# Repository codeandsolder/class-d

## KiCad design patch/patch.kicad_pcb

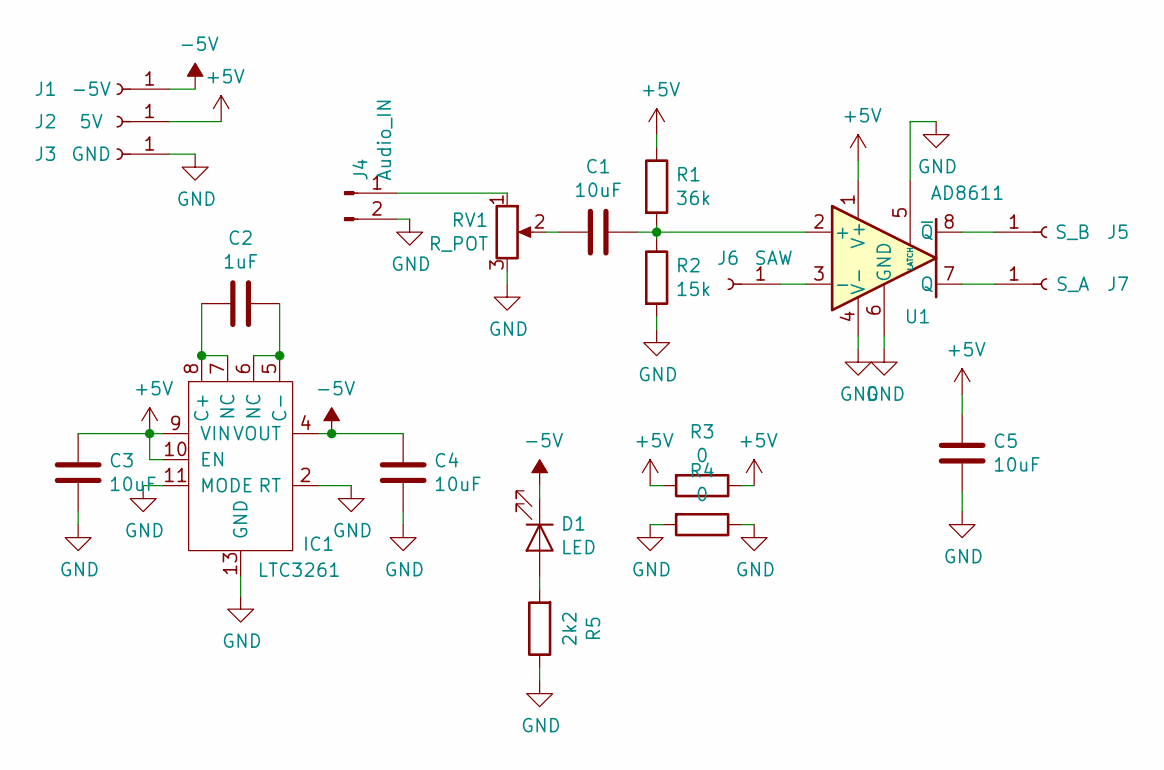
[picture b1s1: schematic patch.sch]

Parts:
C1, C3, C4, C5: 10uF; C_1206_HandSoldering
C2: 1uF; C_1206_HandSoldering
D1: LED; LED_1206_HandSoldering
IC1: LTC3261; MSOP-12-1EP_3x4mm_Pitch0.65mm
J1: -5V; SolderWirePad_single_SMD_5x10mm
J2: 5V; SolderWirePad_single_SMD_5x10mm
J3: GND; SolderWirePad_single_SMD_5x10mm
J4: Audio_IN; Pin_Header_Straight_1x02_Pitch2.54mm
J5: S_B; SolderWirePad_single_SMD_5x10mm
J6: SAW; SolderWirePad_single_SMD_5x10mm
J7: S_A; SolderWirePad_single_SMD_5x10mm
R1: 36k; R_1206_HandSoldering
R2: 15k; R_1206_HandSoldering
R3, R4: 0; R_1206_HandSoldering
R5: 2k2; R_1206_HandSoldering
RV1: R_POT; Potentiometer_Trimmer_Bourns_3266Y
U1: AD8611; SOIC-8_3.9x4.9mm_Pitch1.27mm

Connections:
+5V: C3.2, C5.2, IC1.9 (VIN), IC1.10 (EN), J2.1, R1.1, R3.1, R3.2, U1.1 (V+)
-5V: C4.2, D1.1 (K), IC1.4 (VOUT), J1.1
GND: C3.1, C4.1, C5.1, IC1.2 (RT), IC1.11 (MODE), IC1.13 (GND), J3.1, J4.2, R2.2, R4.1, R4.2, R5.1, RV1.3, U1.4 (V-), U1.5 (LATCH), U1.6 (GND)
unnamed: C1.1, RV1.2
unnamed: C1.2, R1.2, R2.1, U1.2 (+)
unnamed: C2.1, IC1.5 (C-), IC1.6 (NC)
unnamed: C2.2, IC1.7 (NC), IC1.8 (C+)
unnamed: D1.2 (A), R5.2
unnamed: J4.1, RV1.1
unnamed: J5.1, U1.8 (~Q)
unnamed: J6.1, U1.3 (-)
unnamed: J7.1, U1.7 (Q)

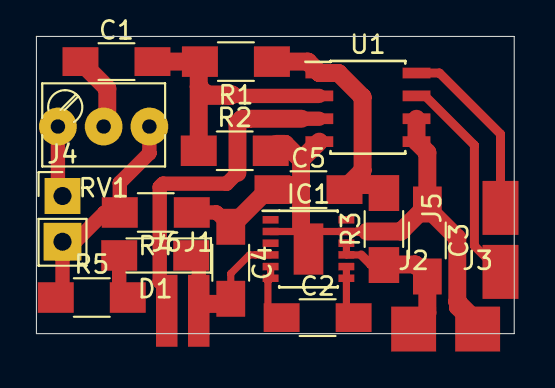
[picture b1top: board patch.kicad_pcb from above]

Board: 2 copper layers, 26.5 x 16.5 mm, 21 parts (0 on the bottom side), 12 nets.

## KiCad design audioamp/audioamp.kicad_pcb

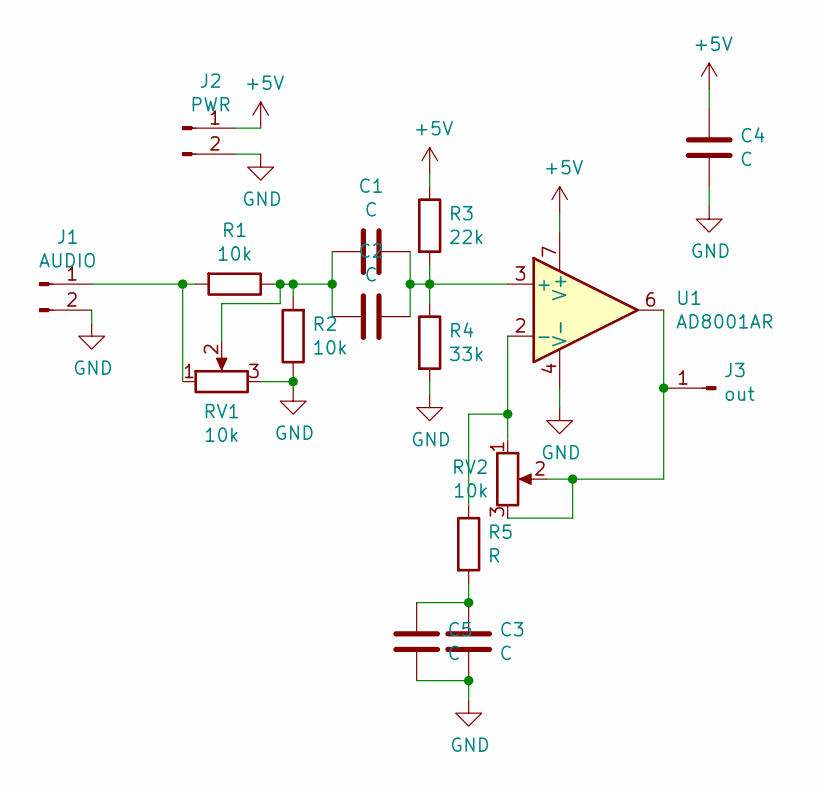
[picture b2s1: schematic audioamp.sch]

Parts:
C1, C2, C3, C4, C5: C; C_1206_3216Metric_Pad1.42x1.75mm_HandSolder
J1: AUDIO; PinHeader_1x02_P2.54mm_Vertical
J2: PWR; PinHeader_1x02_P2.54mm_Vertical
J3: out; PinHeader_1x01_P2.54mm_Vertical
R1, R2: 10k; R_1206_3216Metric_Pad1.42x1.75mm_HandSolder
R3: 22k; R_1206_3216Metric_Pad1.42x1.75mm_HandSolder
R4: 33k; R_1206_3216Metric_Pad1.42x1.75mm_HandSolder
R5: R; R_1206_3216Metric_Pad1.42x1.75mm_HandSolder
RV1: 10k; Potentiometer_Alps_RK163_Single_Horizontal
RV2: 10k; Potentiometer_Bourns_3296W_Vertical
U1: AD8001AR; SOIC-8_3.9x4.9mm_P1.27mm

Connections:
+5V: C4.1, J2.1, R3.1, U1.7 (V+)
GND: C3.2, C4.2, C5.2, J1.2, J2.2, R2.1, R4.2, RV1.3, U1.4 (V-)
unnamed: C1.1, C2.1, R1.1, R2.2, RV1.2
unnamed: C1.2, C2.2, R3.2, R4.1, U1.3 (+)
unnamed: C3.1, C5.1, R5.2
unnamed: J1.1, R1.2, RV1.1
unnamed: J3.1, RV2.2, RV2.3, U1.6
unnamed: R5.1, RV2.1, U1.2 (-)

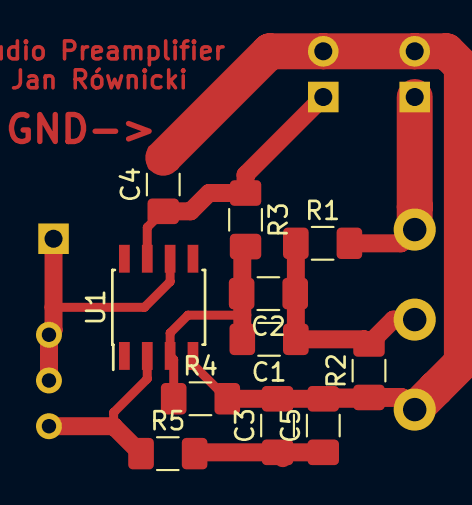
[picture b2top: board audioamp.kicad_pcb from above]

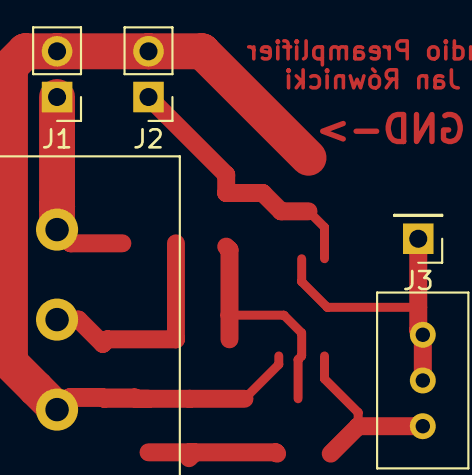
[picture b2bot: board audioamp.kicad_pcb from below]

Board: 2 copper layers, 16 parts (5 on the bottom side), 8 nets.

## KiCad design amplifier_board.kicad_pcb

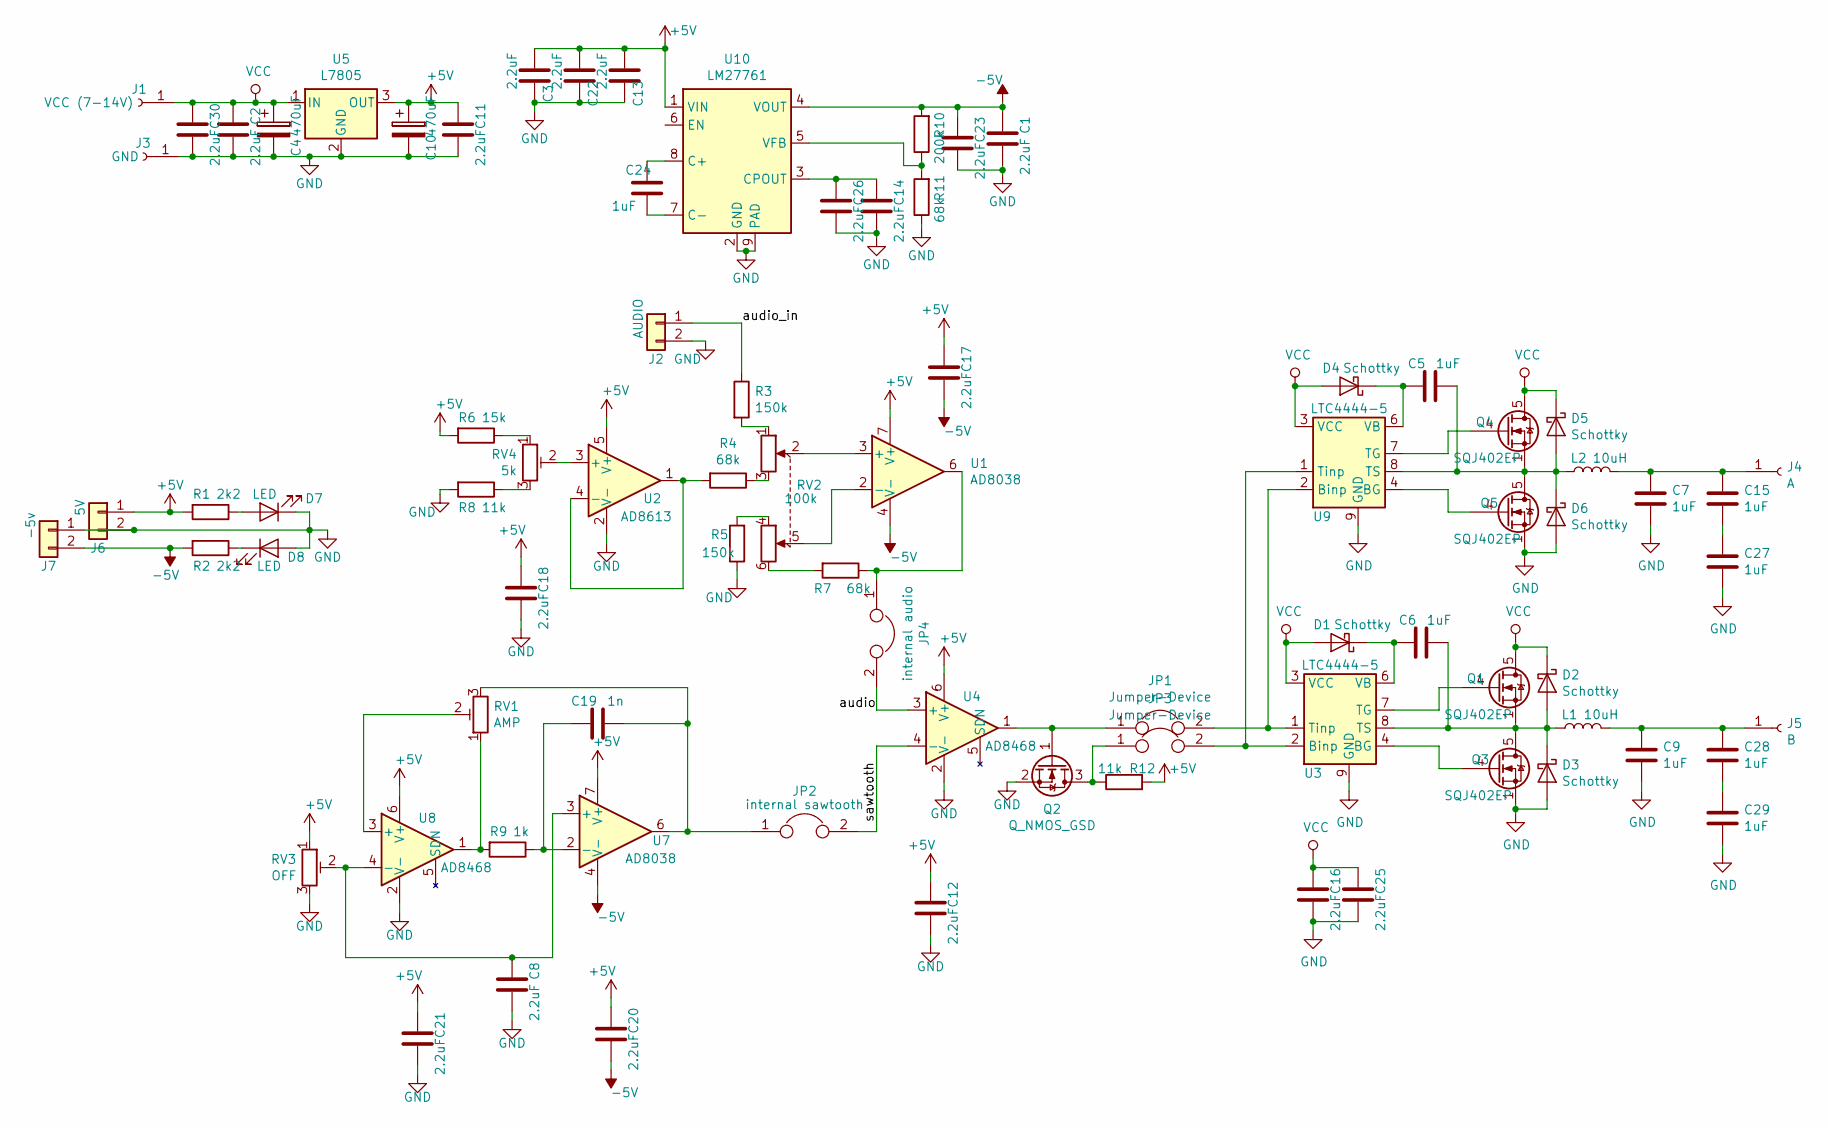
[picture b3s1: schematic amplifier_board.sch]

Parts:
C1, C2, C3, C8, C11, C12, C13, C14, C16, C17, C18, C20, C21, C22, C23, C25, C26, C30: 2.2uF; C_1206_HandSoldering
C4, C10: 470uF; CP_Elec_8x10
C5, C6, C7, C9, C15, C24, C27, C28, C29: 1uF; C_1206_HandSoldering
C19: 1n; C_1206_HandSoldering
D1, D2, D3, D4, D5, D6: Schottky; D_SMA-SMB_Universal_Handsoldering
D7, D8: LED; LED_1206_HandSoldering
J1: VCC (7-14V); SolderWirePad_single_SMD_5x10mm
J2: AUDIO; Pin_Header_Angled_1x02_Pitch2.54mm
J3: GND; SolderWirePad_single_SMD_5x10mm
J4: A; SolderWirePad_single_SMD_5x10mm
J5: B; SolderWirePad_single_SMD_5x10mm
J6: 5V; Pin_Header_Straight_1x02_Pitch2.54mm
J7: -5v; Pin_Header_Straight_1x02_Pitch2.54mm
JP1, JP3: Jumper-Device; Pin_Header_Straight_1x02_Pitch2.54mm
JP2: internal sawtooth; Pin_Header_Straight_1x02_Pitch2.54mm
JP4: internal audio; Pin_Header_Straight_1x02_Pitch2.54mm
L1, L2: 10uH; Choke_Toroid_8x16mm_Vertical
Q1, Q3, Q4, Q5: SQJ402EP; SO-8_PowerPAK_Vishay_Single
Q2: Q_NMOS_GSD; SOT-23
R1, R2: 2k2; R_1206_HandSoldering
R3, R5: 150k; R_1206_HandSoldering
R4, R7, R11: 68k; R_1206_HandSoldering
R6: 15k; R_1206_HandSoldering
R8, R12: 11k; R_1206_HandSoldering
R9: 1k; R_1206_HandSoldering
R10: 200k; R_1206_HandSoldering
RV1: AMP; Pin_Header_Straight_1x03_Pitch2.54mm
RV2: 100k; Potentiometer_Alps_RK163_Double_Vertical
RV3: OFF; Pin_Header_Straight_1x03_Pitch2.54mm
RV4: 5k; Pin_Header_Straight_1x03_Pitch2.54mm
U1, U7: AD8038; SOIC-8_3.9x4.9mm_Pitch1.27mm
U2: AD8613; SOT-23-5_HandSoldering
U3, U9: LTC4444-5; MSOP-8-1EP_3x3mm_Pitch0.65mm
U4, U8: AD8468; SOT-363_SC-70-6_Handsoldering
U5: L7805; TO-252-2_Rectifier
U10: LM27761; VDFN-8-1EP_2x2mm_Pitch0.5mm

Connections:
+5V: C3.1, C10.1, C11.2, C12.2, C13.1, C17.2, C18.2, C20.2, C21.2, C22.1, J6.1, R1.2, R6.2, R12.2, RV3.1, U1.7 (V+), U2.5 (V+), U4.6 (V+), U5.3 (OUT), U7.7 (V+), U8.6 (V+), U10.1 (VIN)
-5V: C1.2, C17.1, C20.1, C23.2, J7.2, R2.2, R10.2, U1.4 (V-), U7.4 (V-), U10.4 (VOUT)
/audio: JP4.2, U4.3 (+)
/audio_in: J2.1, R3.1
/sawtooth: JP2.2, U4.4 (-)
GND: C1.1, C2.1, C3.2, C4.2, C7.2, C8.1, C9.2, C10.2, C11.1, C12.1, C13.2, C14.1, C16.1, C18.1, C21.1, C22.2, C23.1, C25.1, C26.1, C27.2, C29.2, C30.1, D3.2 (A), D6.2 (A), D7.1 (K), D8.2 (A), J2.2, J3.1, J6.2, J7.1, Q2.2 (S), Q3.1 (S), Q3.2 (S), Q3.3 (S), Q5.1 (S), Q5.2 (S), Q5.3 (S), R5.1, R8.2, R11.1, RV3.3, U2.2 (V-), U3.9 (GND), U4.2 (V-), U5.2 (GND), U8.2 (V-), U9.9 (GND), U10.2 (GND), U10.9 (PAD)
unnamed: C5.1, D5.2 (A), D6.1 (K), L2.1, Q4.1 (S), Q4.2 (S), Q4.3 (S), Q5.5 (D), U9.8 (TS)
unnamed: C5.2, D4.1 (K), U9.6 (VB)
unnamed: C6.1, D2.2 (A), D3.1 (K), L1.1, Q1.1 (S), Q1.2 (S), Q1.3 (S), Q3.5 (D), U3.8 (TS)
unnamed: C6.2, D1.1 (K), U3.6 (VB)
unnamed: C8.2, RV3.2, U7.3 (+), U8.4 (-)
unnamed: C14.2, C26.2, U10.3 (CPOUT)
unnamed: C7.1, C15.1, J4.1, L2.2
unnamed: C15.2, C27.1
unnamed: C19.1, JP2.1, RV1.3, U7.6
unnamed: C19.2, R9.1, U7.2 (-)
unnamed: C24.1, U10.8 (C+)
unnamed: C24.2, U10.7 (C-)
unnamed: C9.1, C28.1, J5.1, L1.2
unnamed: C28.2, C29.1
unnamed: D7.2 (A), R1.1
unnamed: D8.1 (K), R2.1
unnamed: JP1.1, Q2.1 (G), U4.1
unnamed: JP1.2, U3.1 (Tinp), U9.2 (Binp)
unnamed: JP3.1, Q2.3 (D), R12.1
unnamed: JP3.2, U3.2 (Binp), U9.1 (Tinp)
unnamed: JP4.1, R7.1, U1.6
unnamed: Q1.4 (G), U3.7 (TG)
unnamed: Q3.4 (G), U3.4 (BG)
unnamed: Q4.4 (G), U9.7 (TG)
unnamed: Q5.4 (G), U9.4 (BG)
unnamed: R3.2, RV2.1
unnamed: R4.1, RV2.3
unnamed: R4.2, U2.1, U2.4 (-)
unnamed: R5.2, RV2.4
unnamed: R6.1, RV4.1
unnamed: R7.2, RV2.6
unnamed: R8.1, RV4.3
unnamed: R9.2, RV1.1, U8.1
unnamed: R10.1, R11.2, U10.5 (VFB)
unnamed: RV1.2, U8.3 (+)
unnamed: RV2.2, U1.3 (+)
unnamed: RV2.5, U1.2 (-)
unnamed: RV4.2, U2.3 (+)
VCC: C2.2, C4.1, C16.2, C25.2, C30.2, D1.2 (A), D2.1 (K), D4.2 (A), D5.1 (K), J1.1, Q1.5 (D), Q4.5 (D), U3.3 (VCC), U5.1 (IN), U9.3 (VCC)

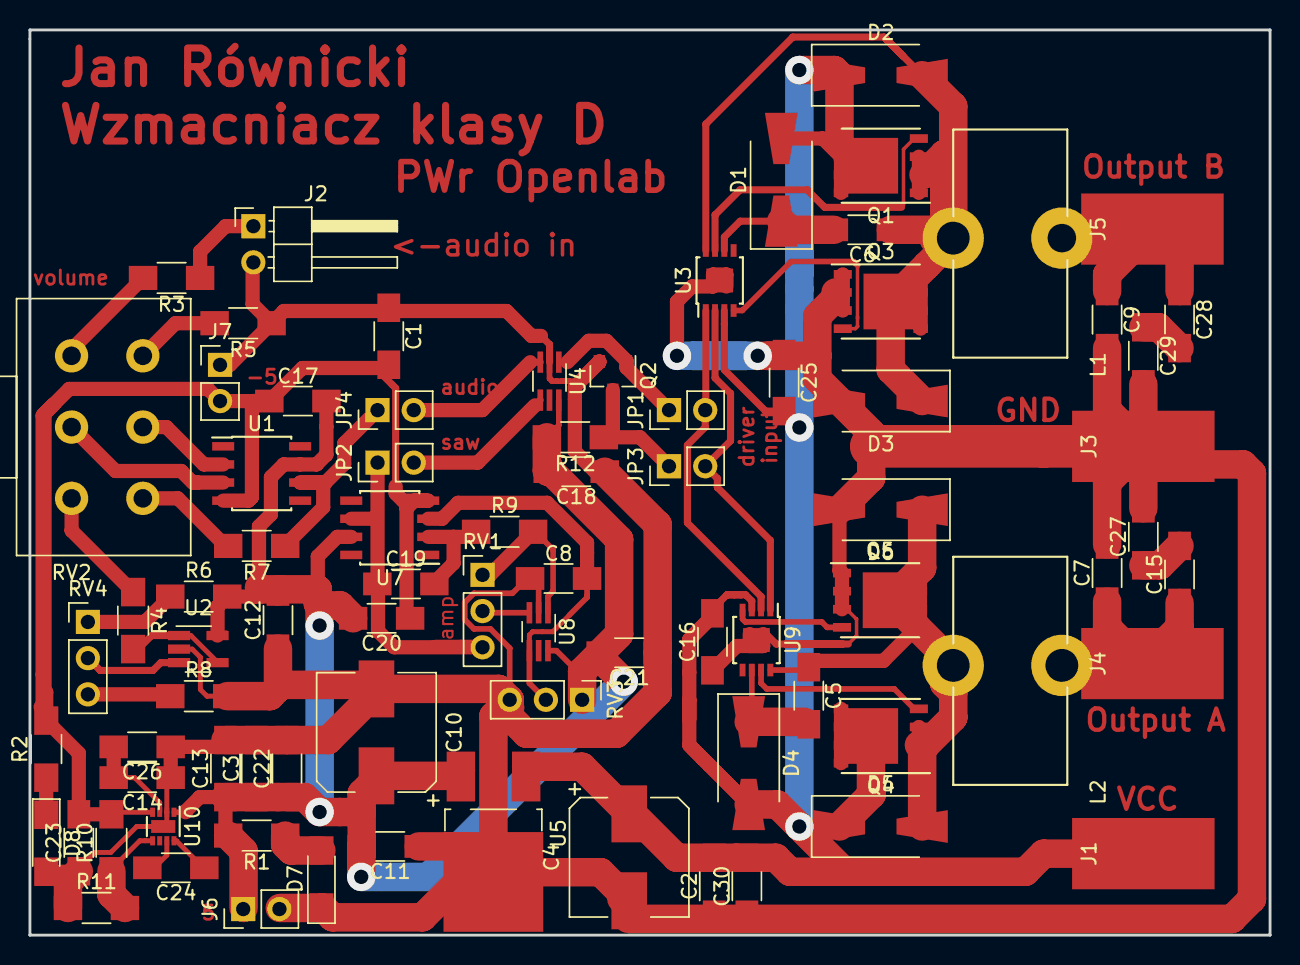
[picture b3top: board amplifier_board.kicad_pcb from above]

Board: 2 copper layers, 87.0 x 63.5 mm, 81 parts (0 on the bottom side), 45 nets.

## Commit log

2019-04-02 files
2019-04-03 more files
2019-05-02 pcb ready
2019-05-04 pcb improvements
2019-05-04 better inverter
2019-05-04 plan B for output filter
2019-05-04 final?
2019-05-04 text and small fixes
2019-05-05 fixes
2019-05-15 updated for manufacture
2019-05-15 better pdf
2019-05-15 actually better pdf
2019-05-16 oops
2019-05-21 patch
